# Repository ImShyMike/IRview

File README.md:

# IRview

A tiny thermal camera with a screen. It's powered by an  ESP32-S3-WROOM-1 with 8mb of PSRAM and 8mb of RAM and uses a Melexis far infrared thermal sensor array with a 32x24 resolution that can measure temperatures from -40 to 300°C and has a 55° FOV and uses a PowerBoost 1000 as a BMS that enables it to use a LiPO battery.

The 320x240px screen at the front is used to display the image data, battery and temperature readings and the buttons are used to switch modes. All pin headers are exposed, even when the case is assembled, to help with debugging. It does not include an usb to UART chip so programming must be done using the exposed TX/RX pins with an external programmer.

---

## Why

Thermal cameras are very expensive and have always felt like magic to me so why not try to make my own on a budget (while also finding out that IR sensors are way more expensive than i expected and that AliExpress always saves the day) :D

---

---

## PCB

---

## Schematic

---

## BOM

| Part      | Qty | Price (USD) | Link |
| --------- | :-: | :---------: | ---- |
|  MLX90640 |  1  | 26.93 - V | https://www.aliexpress.us/item/1005008180135795.html |
| PowerBoost 1000 Charger |  1  | 12.17 - V | https://www.aliexpress.com/item/1005009316907106.html |
| 2.0" 320x240 Color IPS TFT Display |  1  | 7.40 - (54.77 vendor total) | https://www.adafruit.com/product/4311 |
| ESP32-S3-WROOM-1-N8R8 |  2  | 11.03 - V | https://lcsc.com/product-detail/WiFi-Modules_ESPRESSIF-ESP32-S3-WROOM-1-N8R8_C2913201.html |
| AMS1117-3.3 |  5  | 0.87 - (22.78 vendor total) | https://lcsc.com/product-detail/Voltage-Regulators-Linear-Low-Drop-Out-LDO-Regulators_Advanced-Monolithic-Systems-AMS1117-3-3_C6186.html |
| PCB |  1  | 6.16 | - |
| **Total** |     |  **84** |      |

(All total vendor prices include shipping and the down arrow represents merged prices in a single order)

(This BOM does not account for the buttons/headers as i already have those)

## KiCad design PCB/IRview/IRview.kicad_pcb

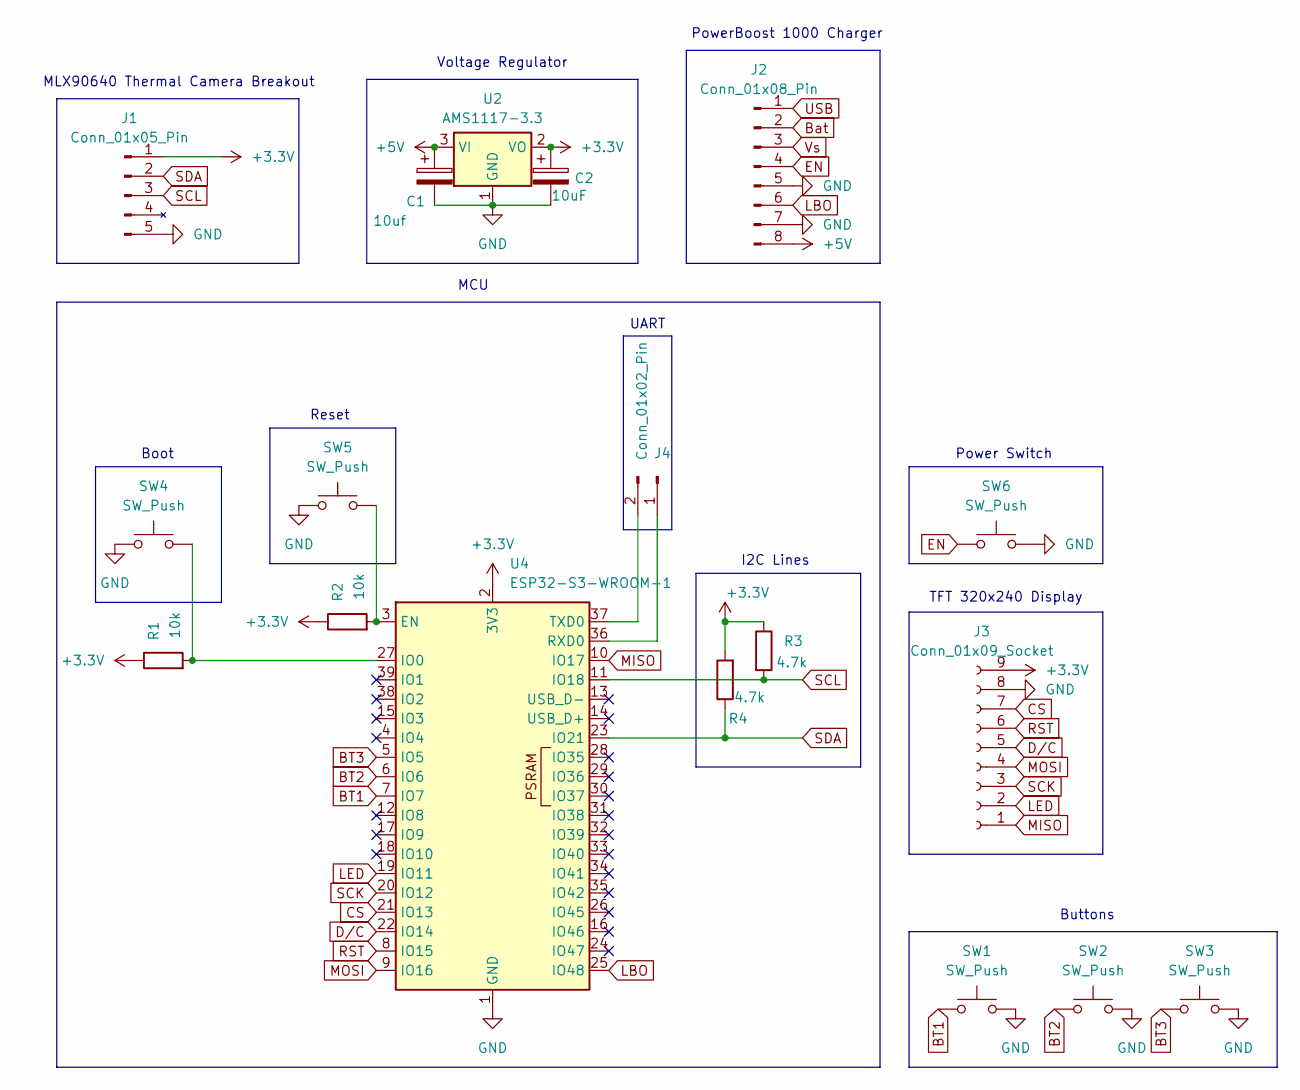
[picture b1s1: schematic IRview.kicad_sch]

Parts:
C1: 10uf; CP_Radial_D4.0mm_P2.00mm
C2: 10uF; CP_Radial_D4.0mm_P2.00mm
J1: Conn_01x05_Pin; PinHeader_1x05_P2.54mm_Vertical
J2: Conn_01x08_Pin; PinHeader_1x08_P2.54mm_Vertical
J3: Conn_01x09_Socket; PinSocket_1x09_P2.54mm_Vertical
J4: Conn_01x02_Pin; PinHeader_1x02_P2.54mm_Vertical
R1, R2: 10k; R_Axial_DIN0207_L6.3mm_D2.5mm_P7.62mm_Horizontal
R3, R4: 4.7k; R_Axial_DIN0207_L6.3mm_D2.5mm_P7.62mm_Horizontal
SW1, SW2, SW3: SW_Push; SW_PUSH_6mm
SW4, SW5: SW_Push; SW_PUSH_6mm_H4.3mm
SW6: SW_Push; SW_DIP_SPSTx01_Slide_9.78x4.72mm_W7.62mm_P2.54mm
U2: AMS1117-3.3; SOT-223-3_TabPin2
U4: ESP32-S3-WROOM-1

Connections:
+3.3V: C2.1, J1.1 (3-6v), J3.9, R1.1, R2.1, R3.1, R4.2, U2.2 (VO), U4.2 (3V3)
+5V: C1.1, J2.8 (5V), U2.3 (VI)
BT1: SW1.1, U4.7 (IO7)
BT2: SW2.1, U4.6 (IO6)
BT3: SW3.1, U4.5 (IO5)
Bat: J2.2 (Bat)
CS: J3.7, U4.21 (IO13)
D/C: J3.5, U4.22 (IO14)
EN: J2.4 (EN), SW6.1
GND: C1.2, C2.2, J1.5 (GND), J2.5 (GND), J2.7 (G), J3.8, SW1.2, SW2.2, SW3.2, SW4.1, SW5.1, SW6.2, U2.1 (GND), U4.1 (GND), U4.40 (GND), U4.41 (GND)
LBO: J2.6 (LBO), U4.25 (IO48)
LED: J3.2, U4.19 (IO11)
MISO: J3.1, U4.10 (IO17)
MOSI: J3.4, U4.9 (IO16)
unnamed: J4.1, U4.36 (RXD0)
unnamed: J4.2, U4.37 (TXD0)
unnamed: R2.2, SW5.2, U4.3 (EN)
unnamed: R1.2, SW4.2, U4.27 (IO0)
RST: J3.6, U4.8 (IO15)
SCK: J3.3, U4.20 (IO12)
SCL: J1.3 (SCL), R3.2, U4.11 (IO18)
SDA: J1.2 (SDA), R4.1, U4.23 (IO21)
USB: J2.1 (USB)
Vs: J2.3 (Vs)

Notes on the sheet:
Voltage Regulator
Boot
PowerBoost 1000 Charger
UART
TFT 320x240 Display
I2C Lines
Buttons
Reset
MCU
MLX90640 Thermal Camera Breakout
Power Switch

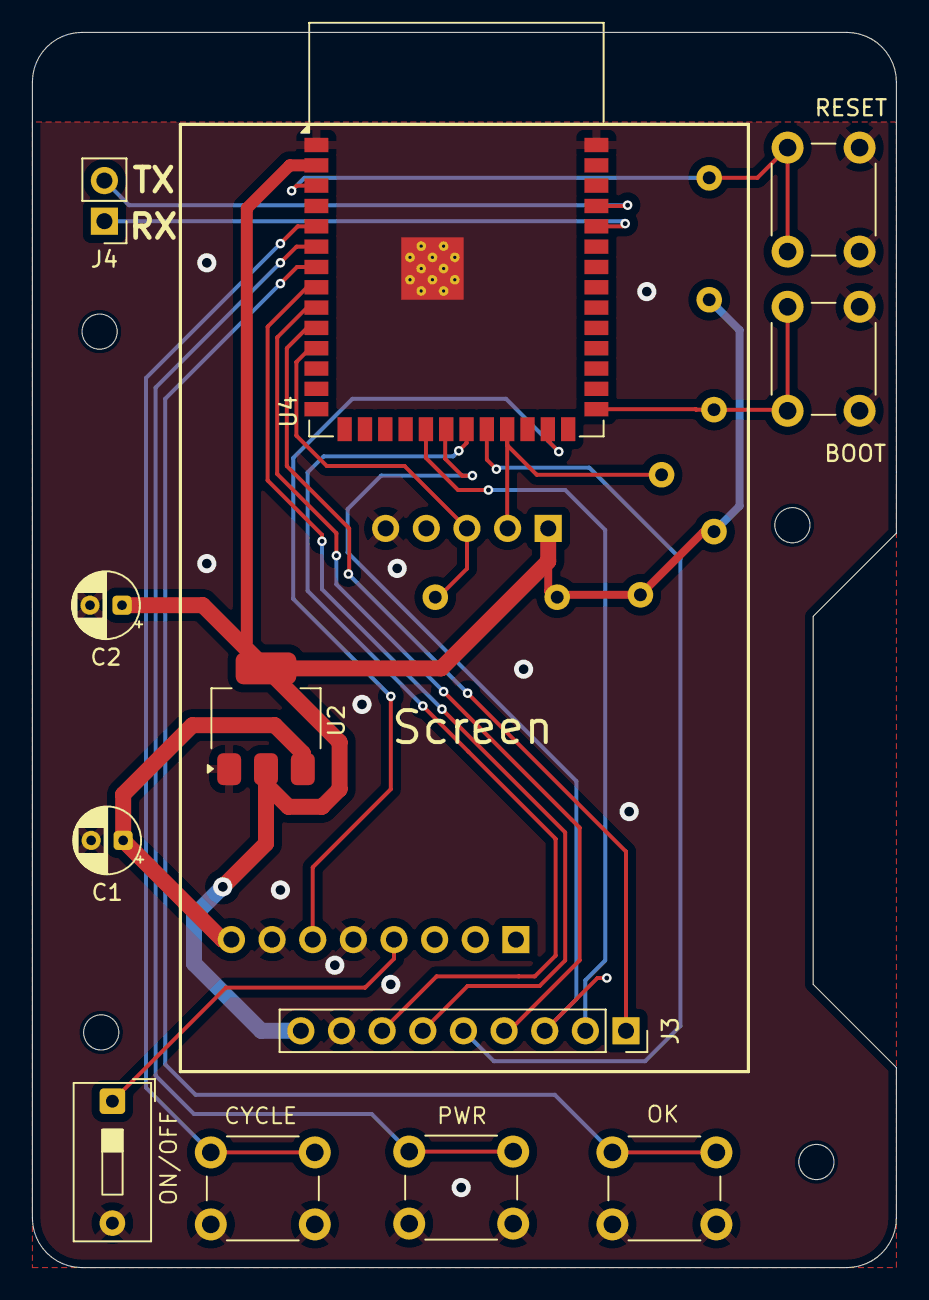
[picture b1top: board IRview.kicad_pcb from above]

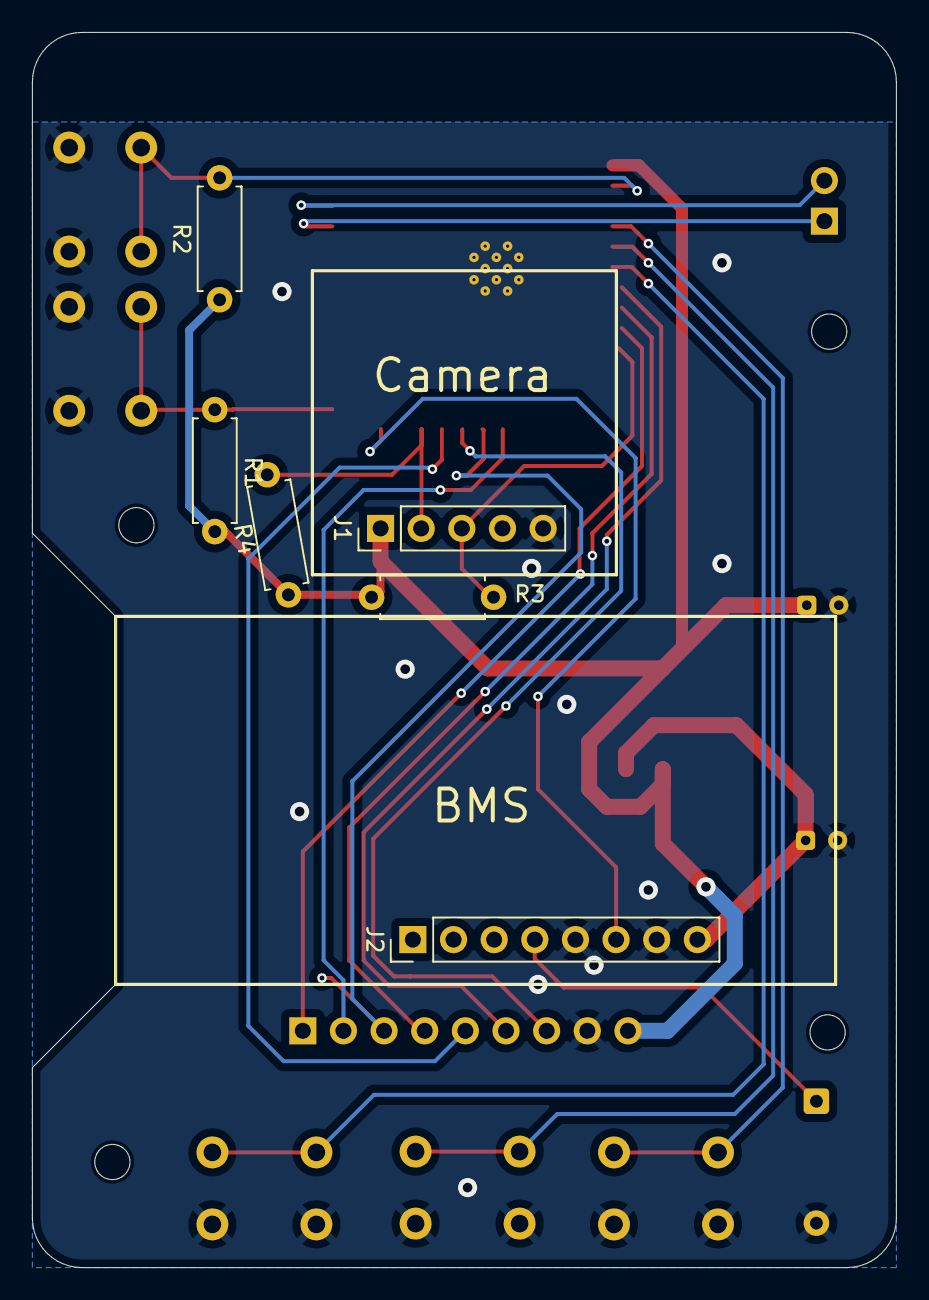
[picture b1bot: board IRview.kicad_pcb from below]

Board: 2 copper layers, 54.0 x 77.2 mm, 18 parts (6 on the bottom side), 21 nets.

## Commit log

2025-07-24 research
2025-07-24 i forgot to commit the other entry mb gng
2025-07-25 cadddddd
    i really need to remember to commit journal changes :sob:
2025-07-25 pcb fixups and changes
2025-07-25 change esp and rewire
2025-07-25 bom and stuff
2025-07-25 change esp name
2025-07-26 very temp firmware
2025-07-26 add schematic to README
2025-07-26 typo
2025-07-26 aliexpress maxxing
2025-07-26 change screen
2025-07-26 add step
2025-07-26 add PCB step file
